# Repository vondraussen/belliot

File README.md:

# Belliot
Door Bell IoT Hardware.
Made with Kicad.

Used to make my door intercom system a bit more smarter. I have a Siedle HT511-01 which I wanted to control from Home Assistant.

## Features
+ Mute bell via relay
+ Actuate door opener via relay
+ One button to mute/unmute bell at the hardware
+ One LED to indicate mute state

## Hardware
+ ESP8266 WeMos D1 Mini
+ AC Optocoupler VOS628A-3T
+ 2x Relais G6K-2F-Y

## Housing
Todo

## Software
The software repository is [belliot_sw](https://github.com/vondraussen/belliot_sw).

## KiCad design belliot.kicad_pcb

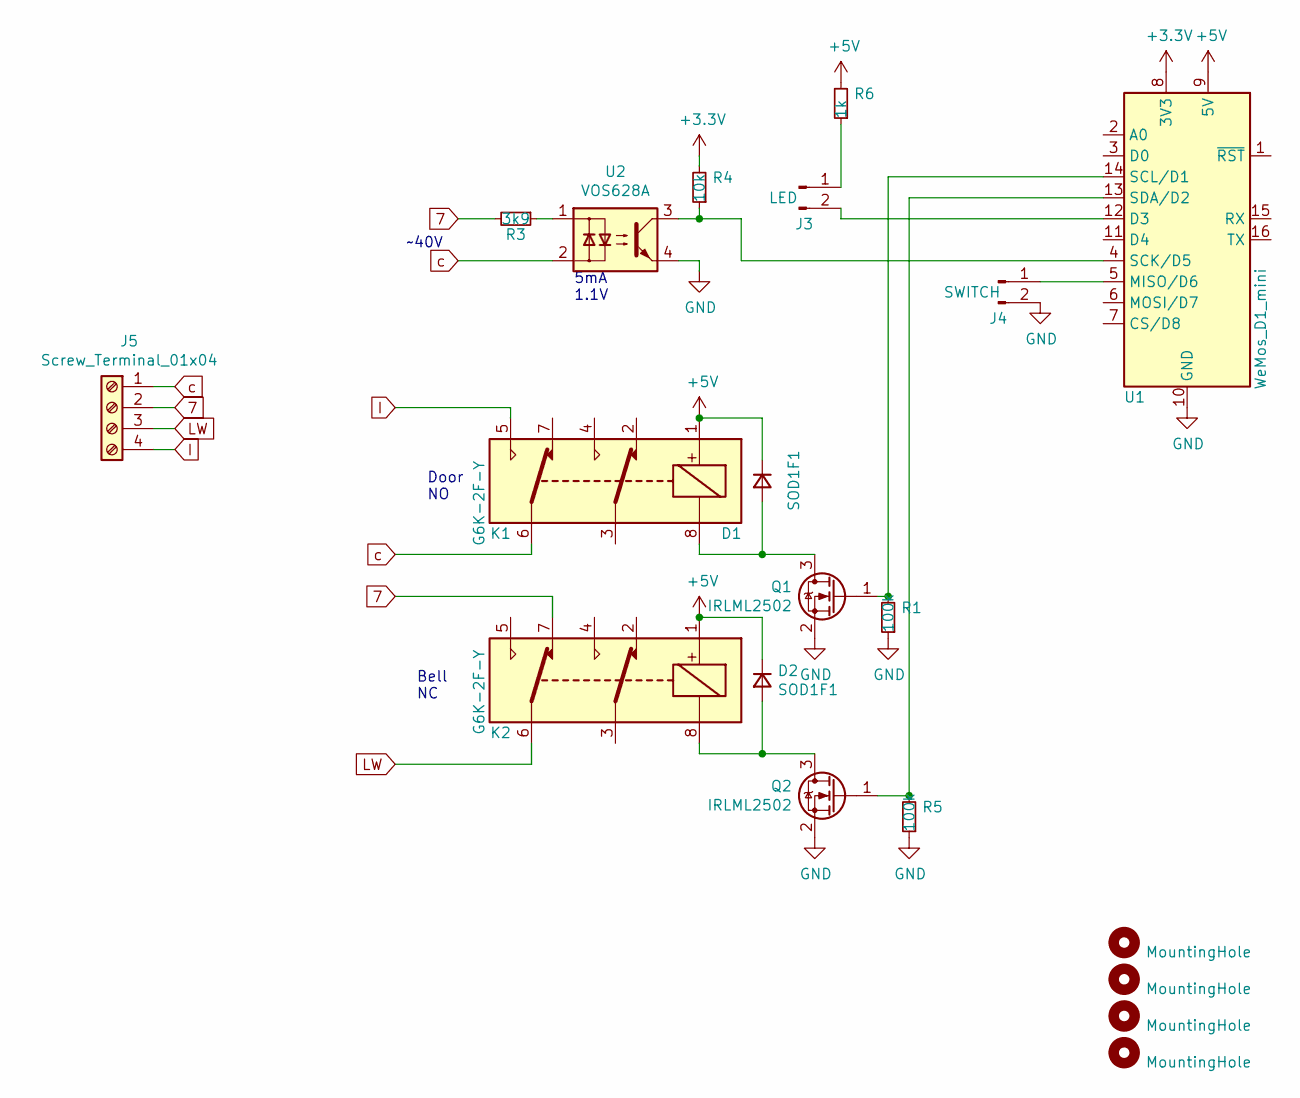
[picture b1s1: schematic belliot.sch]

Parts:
D1, D2: SOD1F1; D_SOD-123F; LCSC C2128
H1, H2, H3, H4: MountingHole; MountingHole_2.7mm
J3: LED; PinHeader_1x02_P2.54mm_Vertical
J4: SWITCH; PinHeader_1x02_P2.54mm_Vertical
J5: Screw_Terminal_01x04; TerminalBlock_Phoenix_MKDS-1,5-4-5.08_1x04_P5.08mm_Horizont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; LCSC C173286
K1, K2: G6K-2F-Y; Relay_DPDT_Omron_G6K-2F-Y; LCSC C231389
Q1, Q2: IRLML2502; SOT-23_Handsoldering; LCSC C8545
R1, R5: 100k; R_0603_1608Metric_Pad0.98x0.95mm_HandSolder; LCSC C25803
R3: 3k9; R_0603_1608Metric_Pad0.98x0.95mm_HandSolder; LCSC C23018
R4: 10k; R_0603_1608Metric_Pad0.98x0.95mm_HandSolder; LCSC C25804
R6: 1k; R_0603_1608Metric_Pad0.98x0.95mm_HandSolder; LCSC C21190
U1: WeMos_D1_mini; WEMOS_D1_mini_light
U2: VOS628A; SSOP-4_4.4x2.6mm_P1.27mm

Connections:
7: J5.2, K2.7, R3.2
+3V3: R4.2, U1.8 (3V3)
+5V: D1.1 (K), D2.1 (K), K1.1, K2.1, R6.2, U1.9 (5V)
GND: J4.2, Q1.2 (S), Q2.2 (S), R1.1, R5.1, U1.10 (GND), U2.4
I: J5.4, K1.5
LW: J5.3, K2.6
unnamed: D1.2 (A), K1.8, Q1.3 (D)
unnamed: D2.2 (A), K2.8, Q2.3 (D)
unnamed: J3.1, R6.1
unnamed: J3.2, U1.12 (D3)
unnamed: J4.1, U1.5 (MISO/D6)
unnamed: Q1.1 (G), R1.2, U1.14 (SCL/D1)
unnamed: Q2.1 (G), R5.2, U1.13 (SDA/D2)
unnamed: R3.1, U2.1
unnamed: R4.1, U1.4 (SCK/D5), U2.3
c: J5.1, K1.6, U2.2

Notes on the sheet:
5mA 1.1V
~~40V
Bell NC
Door NO

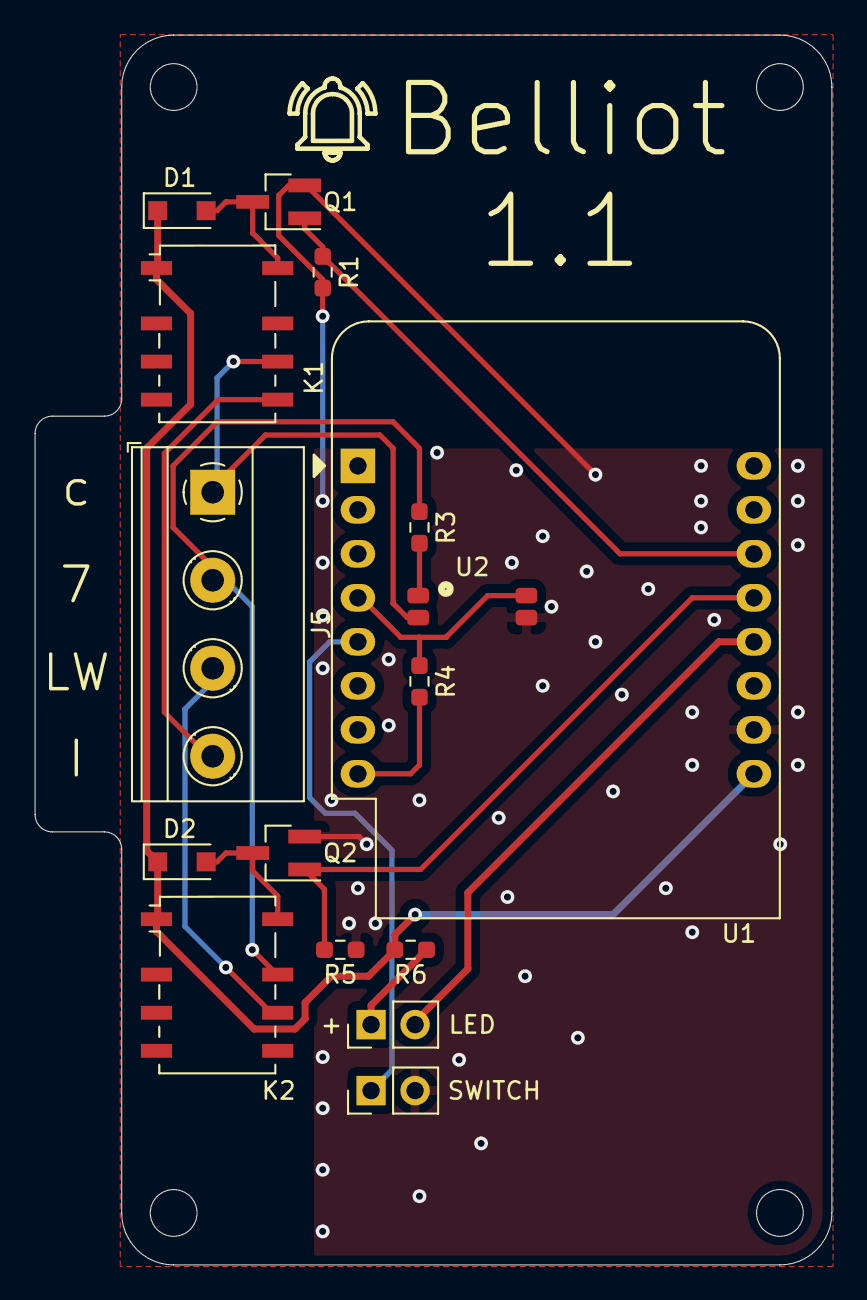
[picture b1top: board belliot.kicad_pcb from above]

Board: 2 copper layers, 46.0 x 71.0 mm, 20 parts (0 on the bottom side), 16 nets.

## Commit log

2021-09-19 init commit
2021-09-20 add d1 3d package
2021-10-03 some improvements
2021-10-03 add pcb pics
2021-10-03 add name and rev to schematic
2021-10-03 add schematic pdf
2021-10-03 add inital housing stl files
2021-10-03 add pics
